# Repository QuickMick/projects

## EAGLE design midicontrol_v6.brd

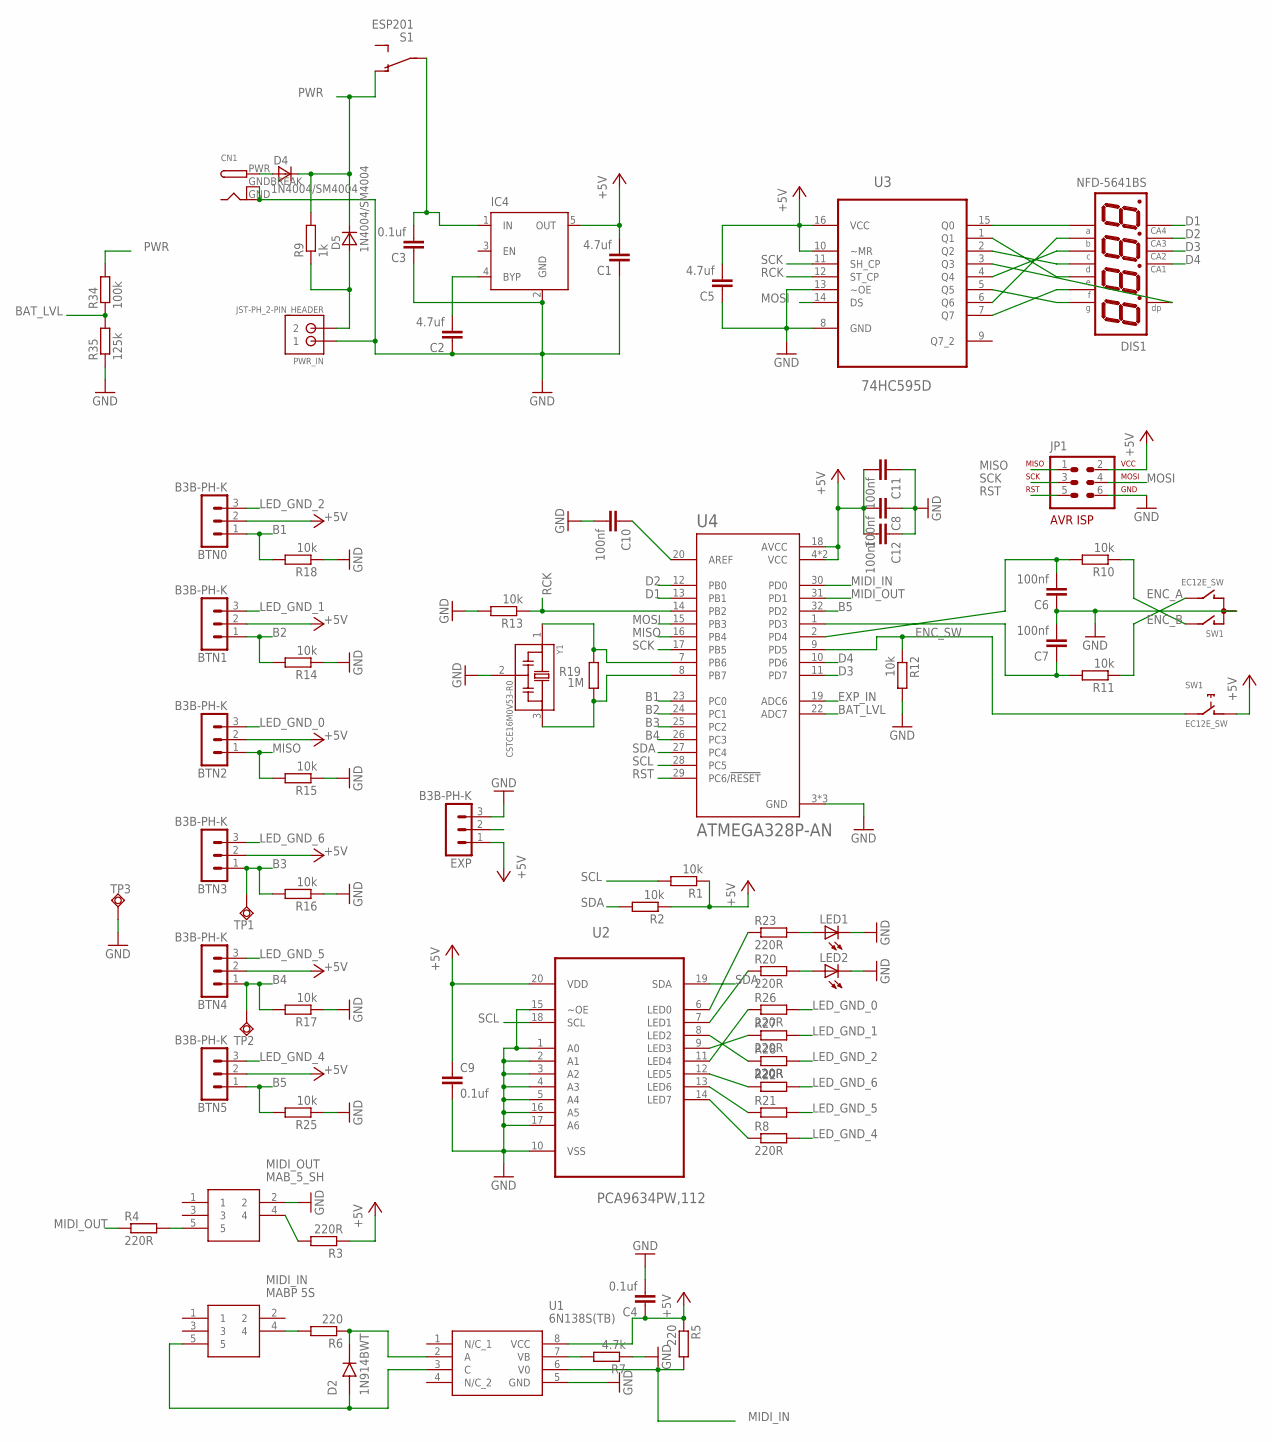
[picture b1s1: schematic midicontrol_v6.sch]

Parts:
BTN0, BTN1, BTN2, BTN3, BTN4, BTN5: B3B-PH-K
C1, C2: 4.7uf; C1206
C3, C4, C9: 0.1uf; C0603
C5: 4.7uf; C0603
C6, C7, C10, C11, C12: 100nf; C0603
C8: 100nf; C1206
CN1: DCBARRELPTH; DCJACK_2MM_PTH
D2: 1N914BWT; SODFL1608X70N
D4, D5: 1N4004/SM4004; MELF-MLL41
DIS1: NFD-5641BS; NFD-5641
EXP: B3B-PH-K
IC4: MIC5219XX; SOT23-5
JP1: AVR-ISP-6HORZ; AVR-ISP-6R
LED1, LED2: LED3MM
MIDI_IN: MABP 5S; MAB-5-SH
MIDI_OUT: MAB_5_SH; MAB-5-SH
PWR_IN: JST-PH_2-PIN_HEADER; JST_B2B-PH_HEADER
R1, R2, R10, R11, R12, R13, R14, R15, R16, R17, R18, R25: 10k; R0603
R3, R4, R8, R20, R21, R22, R23, R26, R27, R28: 220R; R0603
R5, R6: 220; R0603
R7: 4.7k; R0603
R9: 1k; R0603
R19: 1M; R0603-ROUND
R34: 100k; R0603
R35: 125k; R0603
S1: ESP201
SW1: EC12E_SW; ALPS_EC12E_SW
TP1, TP2, TP3: TPSQTP18R; TP18R
U1: 6N138S(TB); SOP254P1030X460-8N
U2: PCA9634PW,112; SOP65P640X110-20N
U3: 74HC595D; SOIC127P600X175-16N
U4: ATMEGA328P-AN; QFP80P900X900X120-32N
Y1: CSTCE16M0V53-R0; OSC_CSTCE16M0V53-R0

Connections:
+5V: BTN0.2, BTN1.2, BTN2.2, BTN3.2, BTN4.2, BTN5.2, C1.2, C4.1, C5.2, C8.2, C9.1, C11.2, C12.2, EXP.1, IC4.5 (OUT), JP1.2, R1.1, R2.1, R3.1, R5.1, SW1.D (1), U1.8 (VCC), U2.20 (VDD), U3.10 (~MR), U3.16 (VCC), U4.4 (VCC), U4.6 (VCC), U4.18 (AVCC)
B1: BTN0.1, R18.2, U4.23 (PC0)
B2: BTN1.1, R14.2, U4.24 (PC1)
B3: BTN3.1, R16.2, TP1.TP, U4.25 (PC2)
B4: BTN4.1, R17.2, TP2.TP, U4.26 (PC3)
B5: BTN5.1, R25.2, U4.32 (PD2)
BAT_LVL: R34.1, R35.2, U4.22 (ADC7)
D1: DIS1.P$6, U4.13 (PB1)
D2: DIS1.P$8, U4.12 (PB0)
D3: DIS1.P$9, U4.11 (PD7)
D4: DIS1.P$12, U4.10 (PD6)
ENC_A: R10.1, SW1.A
ENC_B: R11.1, SW1.B
ENC_SW: R12.1, SW1.E (2), U4.9 (PD5)
EXP_IN: EXP.2, U4.19 (ADC6)
GND: C1.1, C2.1, C3.1, C4.2, C5.1, C6.1, C7.2, C8.1, C9.2, C10.2, C11.1, C12.1, CN1.GND, CN1.GNDBREAK, EXP.3, IC4.2 (GND), JP1.6, LED1.K (C), LED2.K (C), MIDI_OUT.2, PWR_IN.P1 (1), R7.1, R12.2, R13.2, R14.1, R15.1, R16.1, R17.1, R18.1, R25.1, R35.1, SW1.C, TP3.TP, U1.5 (GND), U2.1 (A0), U2.2 (A1), U2.3 (A2), U2.4 (A3), U2.5 (A4), U2.10 (VSS), U2.15 (~OE), U2.16 (A5), U2.17 (A6), U3.8 (GND), U3.13 (~OE), U4.3 (GND), U4.5 (GND), U4.21 (GND), Y1.2
LED_GND_0: BTN2.3, R26.2
LED_GND_1: BTN1.3, R27.2
LED_GND_2: BTN0.3, R28.2
LED_GND_4: BTN5.3, R8.2
LED_GND_5: BTN4.3, R21.2
LED_GND_6: BTN3.3, R22.2
MIDI_IN: R5.2, U1.6 (V0), U4.30 (PD0)
MIDI_OUT: R4.1, U4.31 (PD1)
MISO: BTN2.1, JP1.1, R15.2, U4.16 (PB4)
MOSI: JP1.4, U3.14 (DS), U4.15 (PB3)
unnamed: DIS1.P$11, U3.15 (Q0)
unnamed: DIS1.P$7, U3.6 (Q6)
unnamed: DIS1.P$4, U3.4 (Q4)
unnamed: DIS1.P$2, U3.2 (Q2)
unnamed: DIS1.P$1, U3.1 (Q1)
unnamed: DIS1.P$10, U3.7 (Q7)
unnamed: DIS1.P$5, U3.5 (Q5)
unnamed: DIS1.P$3, U3.3 (Q3)
unnamed: MIDI_OUT.4, R3.2
unnamed: MIDI_OUT.5, R4.2
unnamed: D2.A, MIDI_IN.5, U1.3 (C)
unnamed: D2.C (K), R6.1, U1.2 (A)
unnamed: MIDI_IN.4, R6.2
unnamed: R7.2, U1.7 (VB)
unnamed: C6.2, R10.2, U4.2 (PD4)
unnamed: R19.1, U4.8 (PB7), Y1.3
unnamed: C7.1, R11.2, U4.1 (PD3)
unnamed: D5.A, PWR_IN.P2 (2), R9.1
unnamed: R19.2, U4.7 (PB6), Y1.1
unnamed: C2.2, IC4.4 (BYP)
unnamed: C10.1, U4.20 (AREF)
unnamed: LED2.A, R20.2
unnamed: R8.1, U2.14 (LED7)
unnamed: R21.1, U2.13 (LED6)
unnamed: CN1.PWR, D4.A
unnamed: C3.2, IC4.1 (IN), S1.P$1
unnamed: R22.1, U2.12 (LED5)
unnamed: R26.1, U2.11 (LED4)
unnamed: R27.1, U2.9 (LED3)
unnamed: R28.1, U2.8 (LED2)
unnamed: R20.1, U2.7 (LED1)
unnamed: R23.1, U2.6 (LED0)
unnamed: LED1.A, R23.2
PWR: D4.C, D5.C, R9.2, R34.2, S1.P$3 (O)
RCK: R13.1, U3.12 (ST_CP), U4.14 (PB2)
RST: JP1.5, U4.29 (PC6/!RESET)
SCK: JP1.3, U3.11 (SH_CP), U4.17 (PB5)
SCL: R1.2, U2.18 (SCL), U4.28 (PC5)
SDA: R2.2, U2.19 (SDA), U4.27 (PC4)

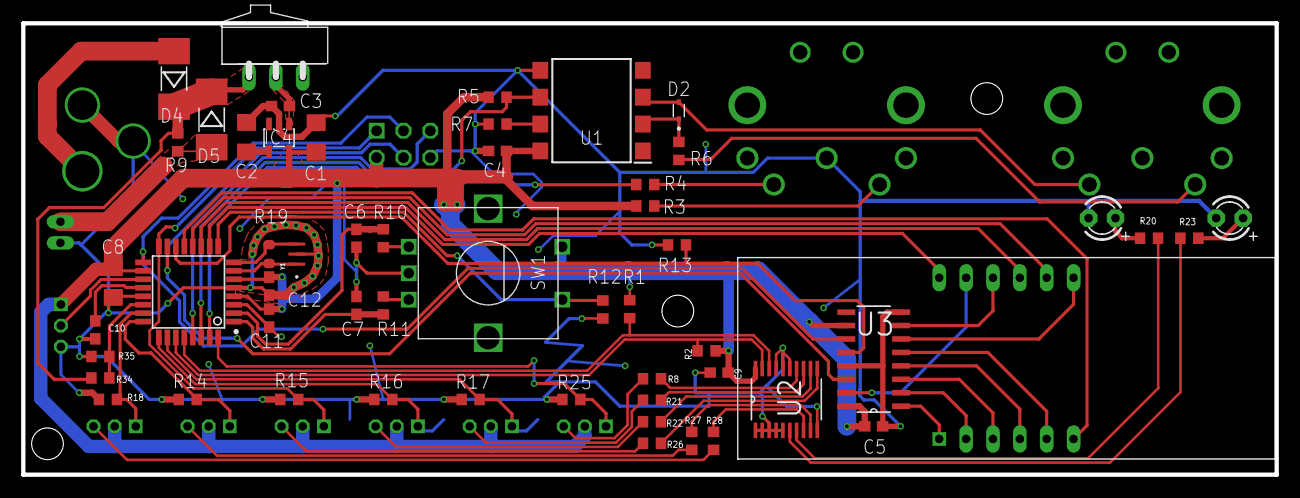
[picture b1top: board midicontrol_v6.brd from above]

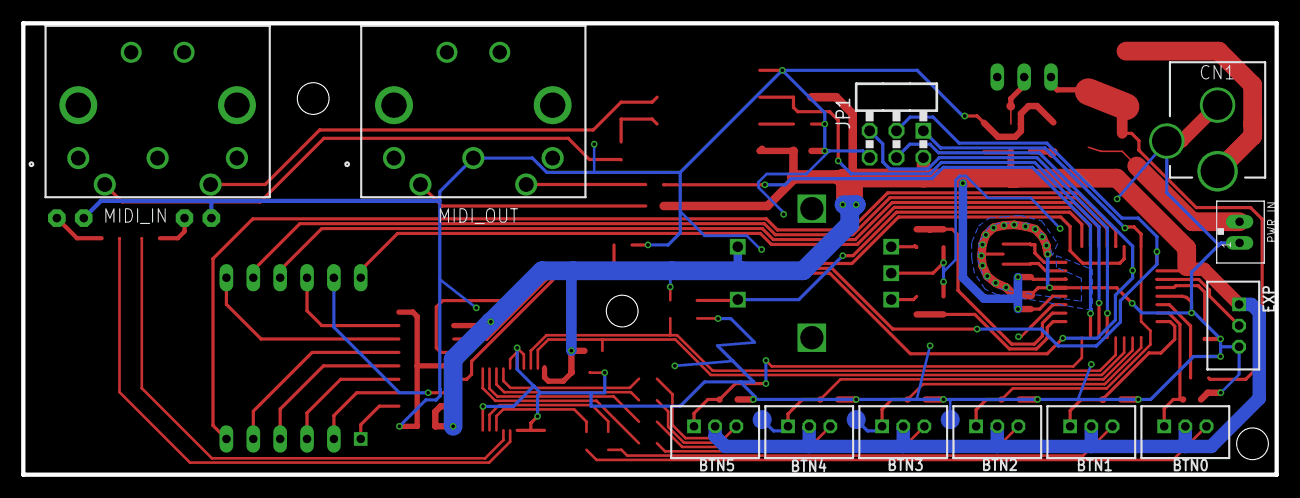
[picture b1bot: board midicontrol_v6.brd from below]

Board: 2 copper layers, 118.5 x 42.7 mm, 70 parts (15 on the bottom side), 65 nets.

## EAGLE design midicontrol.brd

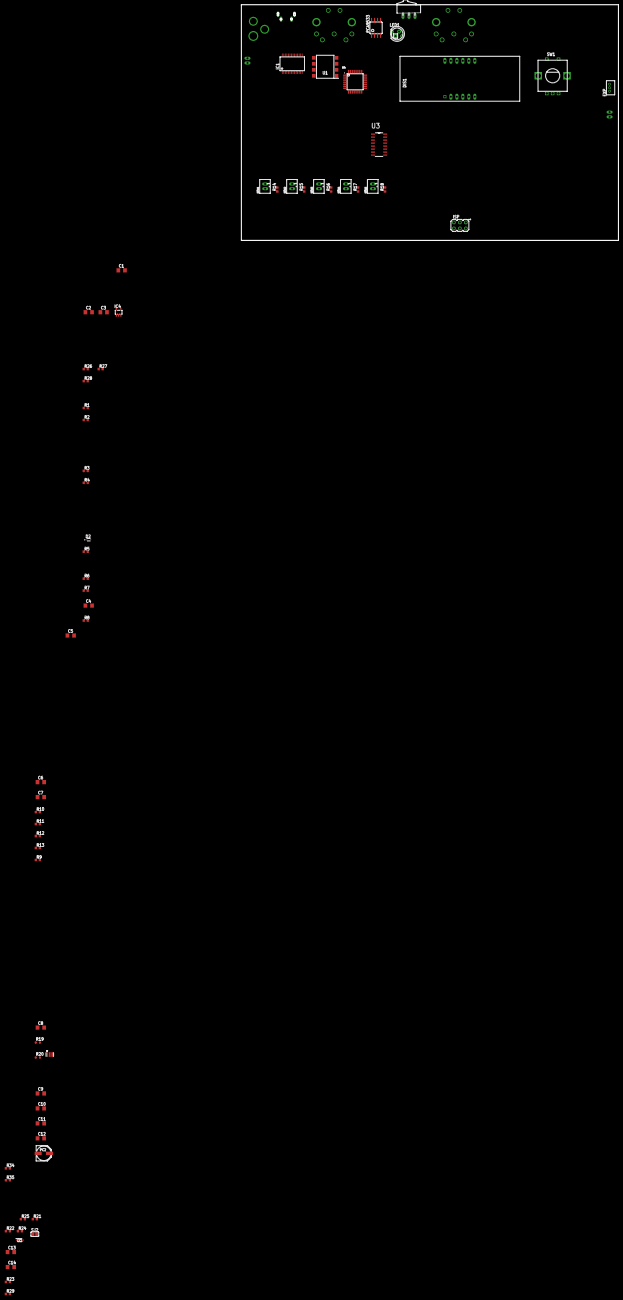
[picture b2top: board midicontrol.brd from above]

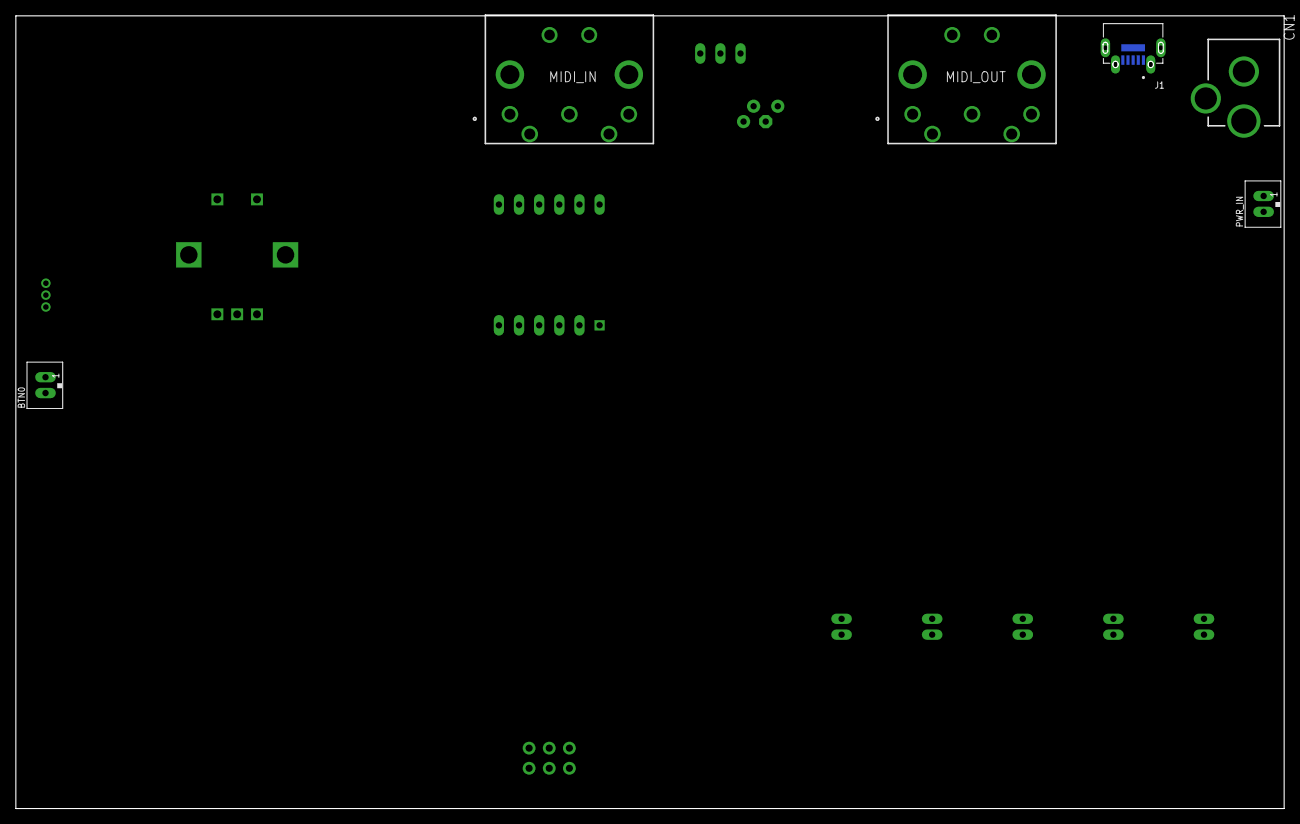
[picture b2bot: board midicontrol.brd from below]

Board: 2 copper layers, 160.0 x 100.0 mm, 73 parts (6 on the bottom side), 63 nets, no tracks yet.

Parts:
BTN0, BTN1, BTN2, BTN3, BTN4, BTN5: JST-PH_2-PIN_HEADER; JST_B2B-PH_HEADER
C1, C2, C5: 4.7uf; C1206
C3, C4, C8: 0.1uf; C1206
C6, C7, C9, C10, C11, C12, C13, C14: 100nf; C1206
CN1: DCJACK_2MM_PTH
D1: BAT60JFILM; SOD2513X117N
D2: 1N914BWT; SODFL1608X70N
DIS1: NFD-5641BS; NFD-5641
EXP: B3B-ZR
IC1: FT232RL-TUBE; SSOP28-LD
IC4: SOT23-5
ISP: AVRISP-6; AVRISP
J1: UJ2-MIBH2-4-SMT-TR; CUI_UJ2-MIBH2-4-SMT-TR
LED1: RGBLED_CA-5MM; LED5MMRGB
MIDI_IN: MABP 5S; MAB-5-SH
MIDI_OUT: MAB_5_SH; MAB-5-SH
PC2: 47u; PANASONIC_D
PCA9533: PCA9533; SOIC8
PWR_IN: JST-PH_2-PIN_HEADER; JST_B2B-PH_HEADER
R1, R2, R9, R10, R11, R12, R13, R14, R15, R16, R17, R18: 10k; R0603
R3, R4, R26, R27, R28: 220R; R0603
R5, R6: 220; R0603
R7: 4.7k; R0603
R8: 2.2k; R0603
R19: 1M; R0603-ROUND
R20: 27R; R0603-ROUND
R21: 1k5; R0603
R22, R24: 22r; R0603
R23, R29: 1k; R0603
R25: 100r; R0603
R34: 100k; R0603
R35: 69k; R0603
S1: ESP201
SJ2: SJ
SW1: EC12E_SW; ALPS_EC12E_SW
U1: 6N138S(TB); SOP254P1030X460-8N
U3: 74HC595D; SOIC127P600X175-16N
U4: ATMEGA328P-AN; QFP80P900X900X120-32N
Y2: 16MHz; RESONATOR

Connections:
+5V: BTN0.P2, BTN1.P2, BTN2.P2, BTN3.P2, BTN4.P2, BTN5.P2, C1.2, C4.1, C5.2, C8.1, C11.2, C12.2, C13.1, C14.1, D1.1, EXP.1, IC1.4, IC1.20, IC4.5, ISP.2, LED1.2, PC2.+, PCA9533.8, R1.1, R2.1, R3.1, R5.1, R8.1, R21.2, SW1.D, U1.8, U3.10, U3.16, U4.4, U4.6, U4.18
B0: BTN0.P1, R9.2, U4.9
B1: BTN1.P1, R14.2, U4.10
B2: BTN2.P1, R15.2, U4.11
B3: BTN3.P1, R16.2, U4.25
B4: BTN4.P1, R17.2, U4.26
B5: BTN5.P1, R18.2
BAT_LVL: R34.1, R35.2, U4.22
D1: DIS1.P$6, U4.12
D2: DIS1.P$8, U4.13
D3: DIS1.P$9, U4.23
D4: DIS1.P$12, U4.24
ENC_A: C7.1, R10.1, R11.2, SW1.B, U4.1
ENC_B: C6.2, R10.2, R11.1, SW1.A, U4.32
ENC_SW: R12.1, SW1.E, U4.2
EXP_IN: EXP.2, U4.19
GND: C1.1, C2.1, C3.1, C4.2, C5.1, C6.1, C7.2, C8.2, C10.2, C11.1, C12.1, C13.2, C14.2, CN1.GND, CN1.GNDBREAK, EXP.3, IC1.7, IC1.18, IC1.21, IC1.25, IC1.26, IC4.2, ISP.6, J1.5, MIDI_OUT.2, PC2.-, PCA9533.4, PWR_IN.P1, R7.1, R9.1, R12.2, R13.2, R14.1, R15.1, R16.1, R17.1, R18.1, R35.1, SJ2.1, SW1.C, U1.5, U3.8, U3.13, U4.3, U4.5, U4.21, Y2.2
MIDI_IN: R5.2, R8.2, R23.1, U1.6, U4.30
MIDI_OUT: R4.1, R29.1, U4.31
MISO: ISP.1, U4.16
MOSI: ISP.4, U3.14, U4.15
unnamed: DIS1.P$11, U3.15
unnamed: DIS1.P$7, U3.1
unnamed: DIS1.P$4, U3.2
unnamed: DIS1.P$2, U3.3
unnamed: DIS1.P$1, U3.4
unnamed: DIS1.P$10, U3.5
unnamed: DIS1.P$5, U3.6
unnamed: DIS1.P$3, U3.7
unnamed: MIDI_OUT.4, R3.2
unnamed: MIDI_OUT.5, R4.2
unnamed: D2.A, MIDI_IN.5, U1.3
unnamed: D2.C, R6.1, U1.2
unnamed: MIDI_IN.4, R6.2
unnamed: R7.2, U1.7
unnamed: LED1.1, R26.2
unnamed: R20.1, U4.7
unnamed: LED1.3, R27.2
unnamed: LED1.4, R28.2
unnamed: IC1.1, R23.2
unnamed: C2.2, IC4.4
unnamed: C10.1, U4.20
unnamed: PCA9533.1, R26.1
unnamed: PCA9533.2, R27.1
unnamed: PCA9533.3, R28.1
unnamed: IC1.5, R29.2
unnamed: C3.2, IC4.1, S1.P$1
unnamed: J1.3, R21.1, R24.2
unnamed: C9.2, IC1.2
unnamed: D1.2, J1.1
unnamed: R25.1, SJ2.2
unnamed: J1.2, R22.2
unnamed: IC1.16, R22.1
unnamed: IC1.15, R24.1
unnamed: J1.SH1, J1.SH2, J1.SH3, J1.SH4, J1.SH5, R25.2
PWR: CN1.PWR, PWR_IN.P2, R34.2, S1.P$3
RCK: R13.1, U3.12, U4.14
RST: C9.1, ISP.5, U4.29
SCK: ISP.3, U3.11, U4.17
SCL: PCA9533.6, R1.2, U4.28
SDA: PCA9533.7, R2.2, U4.27
XT1: R19.1, R20.2, Y2.3
XTAL2: R19.2, U4.8, Y2.1

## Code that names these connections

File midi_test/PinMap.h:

#ifndef __pinmap__
#define __pinmap__

// FootSwitches
#define BTN_0 A0
#define BTN_1 A1
#define BTN_2 12
#define BTN_3 A2
#define BTN_4 A3
#define BTN_5 2

// 7seg display
#define SH_CP 13
#define ST_CP 10
#define DS 11
#define DIGIT_0 9
#define DIGIT_1 8
#define DIGIT_2 7
#define DIGIT_3 6

// encoder
#define ENC_A 3
#define ENC_B 4
#define ENC_SW 5
#endif

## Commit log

2019-05-11 Create fsadasdf
2019-05-11 sdfg
2019-05-18 nearly finished
2019-05-20 finished midiconrol
2019-05-20 finalized it
2019-05-21 changed xh to ph pins
2019-06-07 upatet and finialized for now
2019-06-21 added code for midicontrol

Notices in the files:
parts and their libraries:
con-jst-ph: Copyright (C) 2016, Bob Starr
